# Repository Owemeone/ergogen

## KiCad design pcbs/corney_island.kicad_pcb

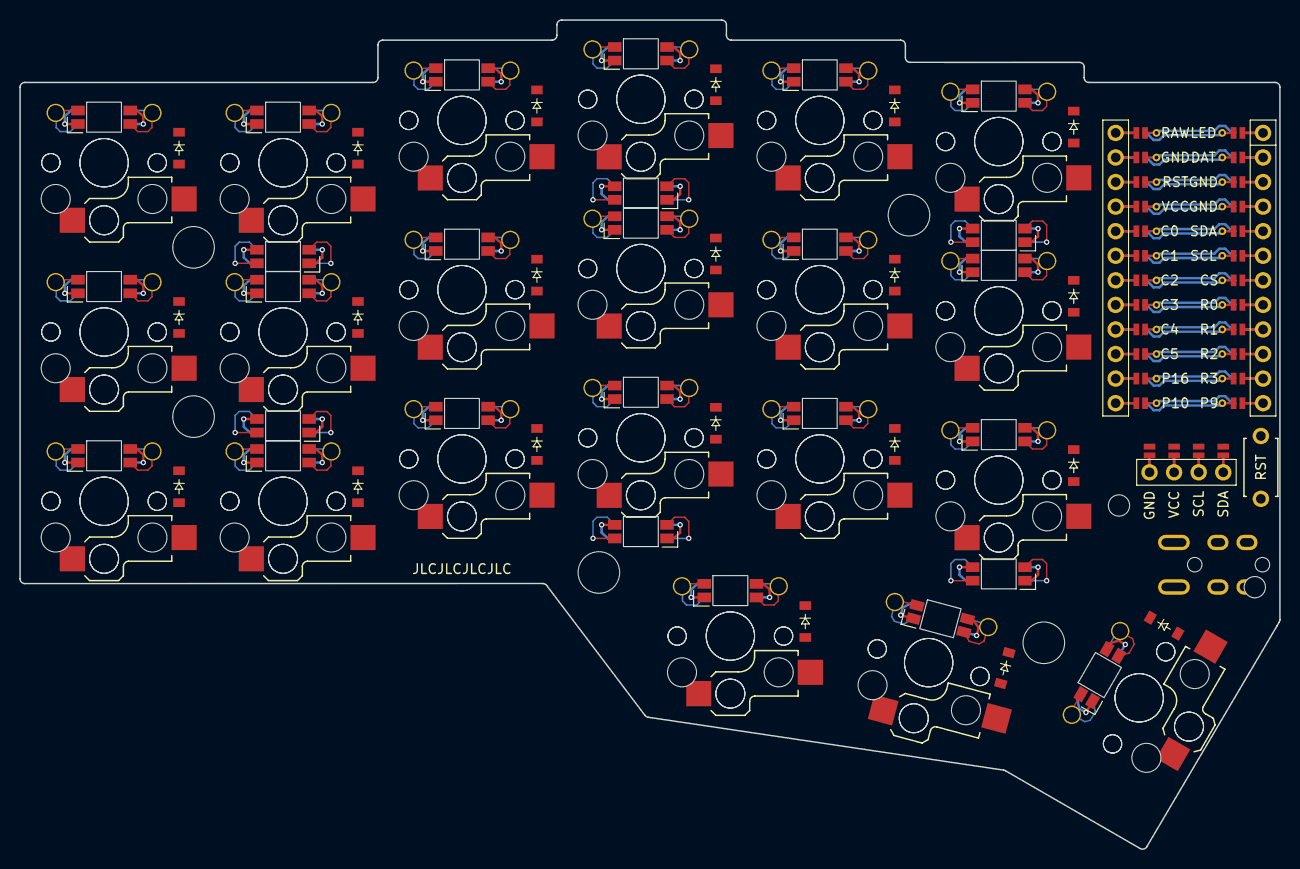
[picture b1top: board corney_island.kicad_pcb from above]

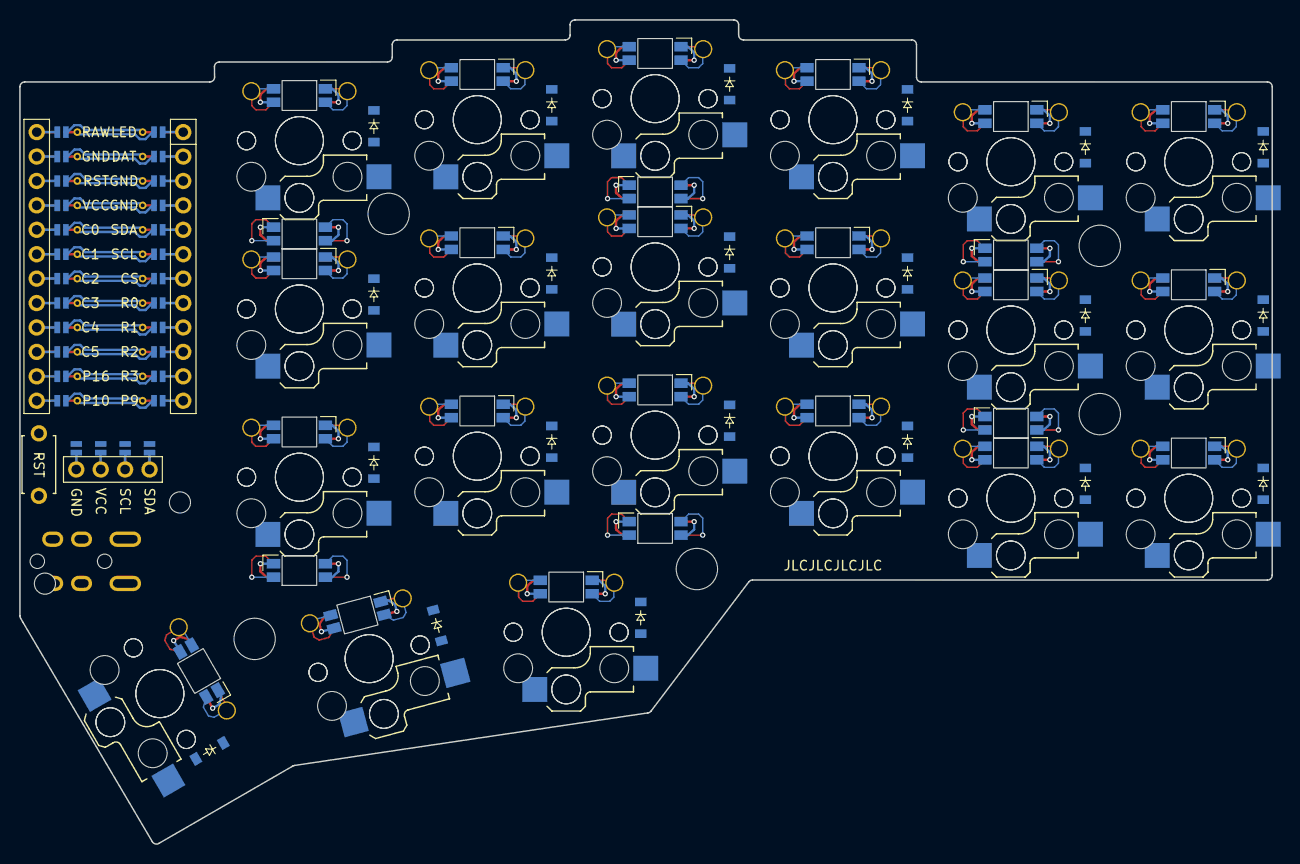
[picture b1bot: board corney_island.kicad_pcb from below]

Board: 2 copper layers, 130.3 x 85.7 mm, 122 parts (69 on the bottom side), 89 nets.

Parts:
D1, D2, D3, D4, D5, D6, D7, D8, D9, D10, D11, D12, D13, D14, D15, D16, D17, D18, D19, D20, D21, D22, D23, D24, D25, D26, D27, D28, D29, D30, D31, D32, D33, D34, D35, D36, D37, D38, D39, D40, D41, D42: diode_tht_sod123
DISP1: display_ssd1306
LED1, LED2, LED3, LED4, LED5, LED6, LED7, LED8, LED9, LED10, LED11, LED12, LED13, LED14, LED15, LED16, LED17, LED18, LED19, LED20, LED21: led_SK6812mini-e (per-key, reversible)
LED22, LED23, LED24, LED25, LED26, LED27: led_SK6812mini-e (underglow, reversible)
MCU1: mcu_nice_nano
MH1, MH2, MH3, MH4, MH5, MH6, MH7: mounting_hole_npth
RST1: reset_switch_tht_top
S1, S2, S3, S4, S5, S6, S7, S8, S9, S10, S11, S12, S13, S14, S15, S16, S17, S18, S19, S20, S21, S22, S23, S24, S25, S26, S27, S28, S29, S30, S31, S32, S33, S34, S35, S36, S37, S38, S39, S40, S41, S42: switch_choc_v1_v2
TRRS1: trrs_pj320a (reversible, symmetric)

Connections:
C0: MCU1.120, S1.1, S2.1, S3.1, S22.1, S23.1, S24.1
C1: MCU1.119, S4.1, S5.1, S6.1, S25.1, S26.1, S27.1
C2: MCU1.118, S7.1, S8.1, S9.1, S28.1, S29.1, S30.1
C3: MCU1.117, S10.1, S11.1, S12.1, S19.1, S31.1, S32.1, S33.1, S40.1
C4: MCU1.116, S13.1, S14.1, S15.1, S20.1, S34.1, S35.1, S36.1, S41.1
C5: MCU1.115, S16.1, S17.1, S18.1, S21.1, S37.1, S38.1, S39.1, S42.1
DAT: MCU1.102, TRRS1.3
DISP1_1: DISP1.1, DISP1.10, DISP1.23
DISP1_2: DISP1.2, DISP1.11, DISP1.22
DISP1_3: DISP1.3, DISP1.12, DISP1.21
DISP1_4: DISP1.4, DISP1.13, DISP1.20
GND: DISP1.14, DISP1.24, LED1.3, LED2.3, LED3.3, LED4.3, LED5.3, LED6.3, LED7.3, LED8.3, LED9.3, LED10.3, LED11.3, LED12.3, LED13.3, LED14.3, LED15.3, LED16.3, LED17.3, LED18.3, LED19.3, LED20.3, LED21.3, LED22.3, LED23.3, LED24.3, LED25.3, LED26.3, LED27.3, MCU1.103, MCU1.104, MCU1.123, RST1.2, TRRS1.2
LED: LED22.4, MCU1.101
LED_1: LED16.4, LED21.2
LED_2: LED16.2, LED17.4
LED_3: LED17.2, LED18.4
LED_4: LED15.4, LED18.2
LED_5: LED14.4, LED15.2
LED_6: LED13.4, LED14.2
LED_7: LED13.2, LED20.4
LED_8: LED19.4, LED20.2
LED_9: LED10.4, LED19.2
LED_10: LED10.2, LED11.4
LED_11: LED11.2, LED12.4
LED_12: LED9.4, LED12.2
LED_13: LED8.4, LED9.2
LED_14: LED7.4, LED8.2
LED_15: LED4.4, LED7.2
LED_16: LED4.2, LED5.4
LED_17: LED5.2, LED6.4
LED_18: LED3.4, LED6.2
LED_19: LED2.4, LED3.2
LED_20: LED1.4, LED2.2
R0: D3.1, D6.1, D9.1, D12.1, D15.1, D18.1, D24.1, D27.1, D30.1, D33.1, D36.1, D39.1, MCU1.108
R1: D2.1, D5.1, D8.1, D11.1, D14.1, D17.1, D23.1, D26.1, D29.1, D32.1, D35.1, D38.1, MCU1.109
R2: D1.1, D4.1, D7.1, D10.1, D13.1, D16.1, D22.1, D25.1, D28.1, D31.1, D34.1, D37.1, MCU1.110
R3: D19.1, D20.1, D21.1, D40.1, D41.1, D42.1, MCU1.111
RST: MCU1.122, RST1.1
SCL: DISP1.16, DISP1.26, MCU1.106
SDA: DISP1.17, DISP1.27, MCU1.105
ULED_1: LED22.2, LED23.4
ULED_2: LED23.2, LED24.4
ULED_3: LED24.2, LED25.4
ULED_4: LED25.2, LED26.4
ULED_5: LED26.2, LED27.4
ULED_6: LED21.4, LED27.2
VCC: DISP1.15, DISP1.25, LED1.1, LED2.1, LED3.1, LED4.1, LED5.1, LED6.1, LED7.1, LED8.1, LED9.1, LED10.1, LED11.1, LED12.1, LED13.1, LED14.1, LED15.1, LED16.1, LED17.1, LED18.1, LED19.1, LED20.1, LED21.1, LED22.1, LED23.1, LED24.1, LED25.1, LED26.1, LED27.1, MCU1.121, TRRS1.4
far_home_B: D21.2, S21.2
far_home_F: D42.2, S42.2
index_bottom_B: D13.2, S13.2
index_bottom_F: D34.2, S34.2
index_home_B: D14.2, S14.2
index_home_F: D35.2, S35.2
index_top_B: D15.2, S15.2
index_top_F: D36.2, S36.2
inner_bottom_B: D16.2, S16.2
inner_bottom_F: D37.2, S37.2
inner_home_B: D17.2, S17.2
inner_home_F: D38.2, S38.2
inner_top_B: D18.2, S18.2
inner_top_F: D39.2, S39.2
mid_home_B: D20.2, S20.2
mid_home_F: D41.2, S41.2
middle_bottom_B: D10.2, S10.2
middle_bottom_F: D31.2, S31.2
middle_home_B: D11.2, S11.2
middle_home_F: D32.2, S32.2
middle_top_B: D12.2, S12.2
middle_top_F: D33.2, S33.2
near_home_B: D19.2, S19.2
near_home_F: D40.2, S40.2
outer_bottom_B: D1.2, S1.2
outer_bottom_F: D22.2, S22.2
outer_home_B: D2.2, S2.2
outer_home_F: D23.2, S23.2
outer_top_B: D3.2, S3.2
outer_top_F: D24.2, S24.2
pinky_bottom_B: D4.2, S4.2
pinky_bottom_F: D25.2, S25.2
pinky_home_B: D5.2, S5.2
pinky_home_F: D26.2, S26.2
pinky_top_B: D6.2, S6.2
pinky_top_F: D27.2, S27.2
ring_bottom_B: D7.2, S7.2
ring_bottom_F: D28.2, S28.2
ring_home_B: D8.2, S8.2
ring_home_F: D29.2, S29.2
ring_top_B: D9.2, S9.2
ring_top_F: D30.2, S30.2

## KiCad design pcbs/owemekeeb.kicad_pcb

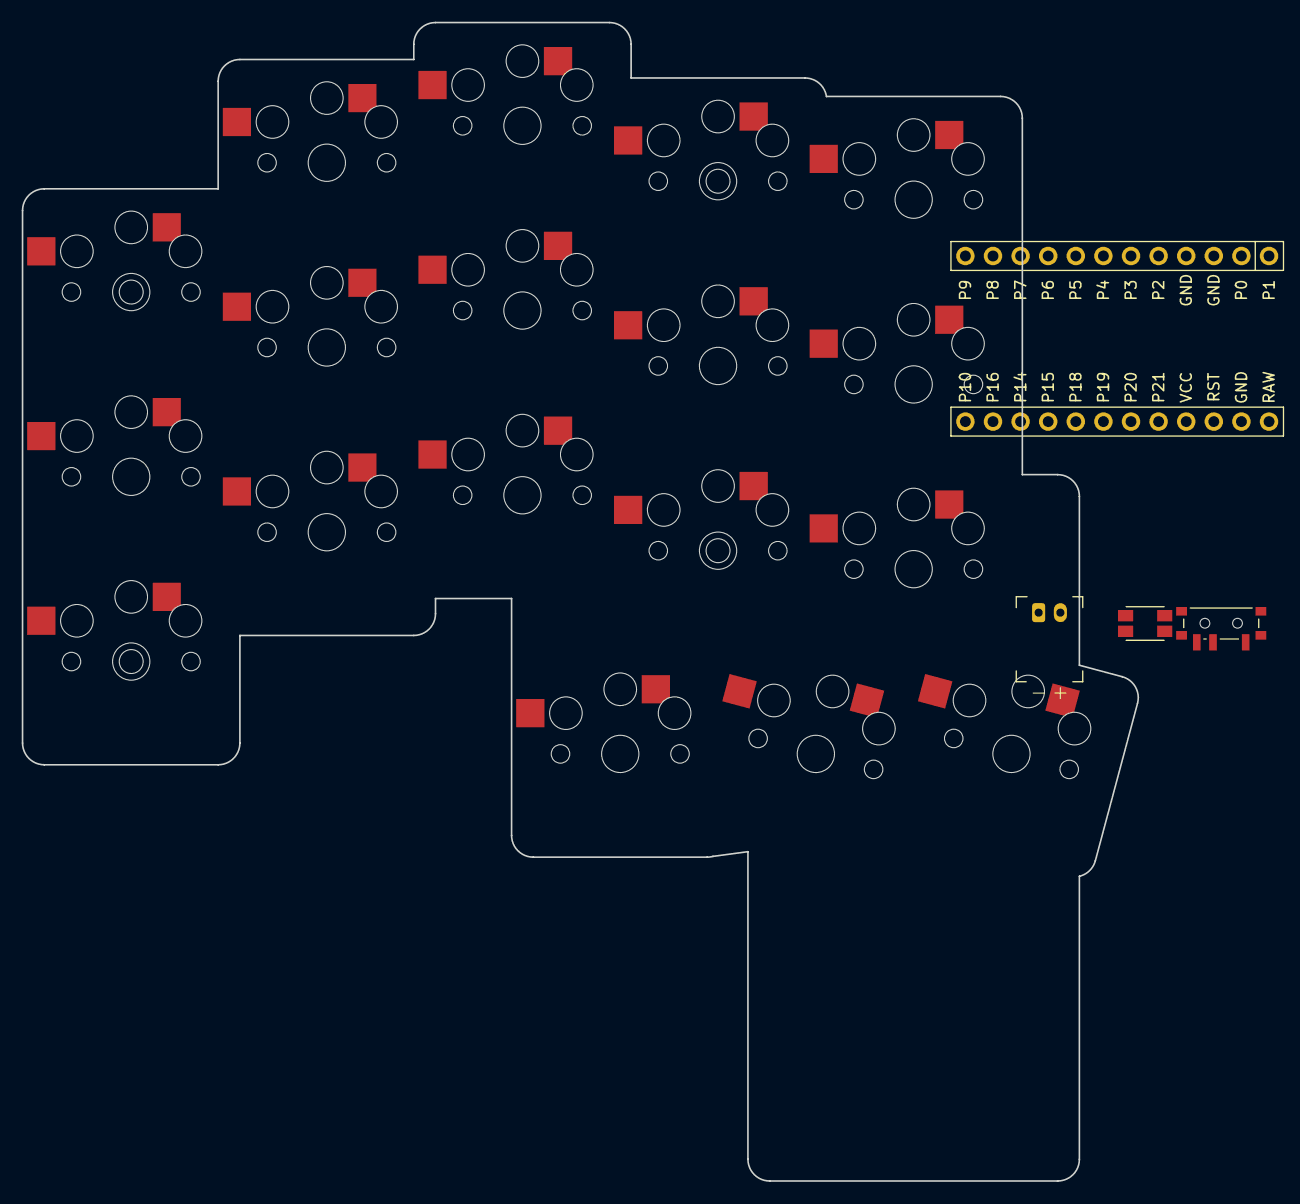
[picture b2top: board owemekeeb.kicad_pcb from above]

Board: 2 copper layers, 102.7 x 106.6 mm, 26 parts (0 on the bottom side), 22 nets, no tracks yet.

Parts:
JST1: battery_connector_jst_ph_2
MCU1: mcu_nice_nano
MH1, MH2, MH3, MH4: mounting_hole_npth
S1, S2, S3, S4, S5, S6, S7, S8, S9, S10, S11, S12, S13, S14, S15, S16, S17, S18: PG1350
SW1: power_switch
SW2: sw_reset_side

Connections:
GND: JST1.1, MCU1.2, MCU1.21, MCU1.22, S1.2, S2.2, S3.2, S4.2, S5.2, S6.2, S7.2, S8.2, S9.2, S10.2, S11.2, S12.2, S13.2, S14.2, S15.2, S16.2, S17.2, S18.2, SW2.1
P0: MCU1.23, S6.1
P1: MCU1.24, S9.1
P2: MCU1.20, S3.1
P3: MCU1.19, S8.1
P4: MCU1.18, S5.1
P5: MCU1.17, S2.1
P6: MCU1.16, S7.1
P7: MCU1.15, S4.1
P8: MCU1.14, S1.1
P9: MCU1.13, S16.1
P10: MCU1.12, S17.1
P14: MCU1.10, S13.1
P15: MCU1.9, S10.1
P16: MCU1.11, S18.1
P18: MCU1.8, S14.1
P19: MCU1.7, S11.1
P20: MCU1.6, S15.1
P21: MCU1.5, S12.1
RAW: MCU1.1, SW1.3, SW1.6
RST: MCU1.3, SW2.2
pos: SW1.2, SW1.5

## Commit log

2022-06-20 Add Owemekeeb
2022-06-20 Updated .gitignore
2022-06-20 package-lock changes
2022-06-21 Cleanup Use variables Better tracing of outline
2022-06-23 Add net class for power
2022-06-23 Update pin assignment
2022-06-24 Add build script based on Samoklava
2022-07-05 Update my keyboard
2022-07-05 Add reference values to vias Rotate PCM12
2022-07-05 Add Paintbrush config
2022-07-05 Add build script for Windows
2022-10-26 Added promicro_dave and workflows
2022-10-26 Minor fix
2022-10-26 Minor fixes again
2022-10-26 Case sensitive?
2022-10-26 temp output
2022-10-27 New steps in workflow - added DRC step - added image generation
2022-10-27 Continue on error for drc
2022-10-27 Upgrade deprecated actions
2022-10-27 Add name to gerber output
2022-10-27 Typo
2022-10-27 nametemplate isn't support in this version of kikit
2022-10-27 Add DRC to kikit fab
2022-10-27 Test DRC on samoklava
2022-10-27 update kikit
2022-10-28 Continue on error for export gerbers, because of drc
2022-10-28 Add workflows for all keyboards
2022-10-28 Error in build all yaml
2022-10-28 next attempt at matrix
2022-10-28 next attempt
2022-10-28 again
2022-10-28 more attempts
2022-10-28 and again
2022-10-28 typo again
2022-10-28 tryout
2022-10-28 keep trying
2022-10-28 How about this
2022-10-28 Wow that where a lot of omissions
2022-10-28 fail fast false
2022-10-28 Set maximum passes for autoroute
2022-10-28 disable drc on gerber export
2022-10-28 paintbrush didn't have a pcb
2022-10-28 Max passes routing
2022-10-28 Fix paintbrush
2022-10-28 Set max autoroute passes
2022-10-28 trying drc fix
2022-10-28 Reverted 0.01 attempt to fix DRC errors
2022-10-29 Attempt to fix drc error with choc footprint
2022-10-29 Fix owmekeeb workflow
2022-10-29 Type
2022-10-29 Add choc pretty
2022-10-29 Type again
2022-10-29 Newish choc pretty
2022-10-30 Fix keyboard array for all workflows
2022-10-30 Owemeone uses choc again
2022-10-30 Keyboard vs keyboards
2022-10-30 Ooops
2022-10-30 Rebuild on yaml change
2022-10-30 Repeat last
2022-10-30 Try to trigger build
2022-10-30 Guess what? Typo
2022-10-30 Trigger again
2023-08-08 Fix owmekeeb for v4
2023-08-08 Trying without a desktop.. That will work
2023-08-08 Skip old build
2023-08-08 Fix order
2023-08-08 Typo owemekeeb
2023-08-08 config import
2023-11-25 Fix update issues
2023-11-25 samples
2023-11-25 udpate promicro pretty
2023-11-25 fixes
2023-11-25 Add intersect aggregator (#102)
    * Added intersect aggregator
    * Addressed stylistic PR feedback
    * Set the rotation of the intersected point to the second point’s rotation
    * Revert "Set the rotation of the intersected point to the second point’s rotation"
    This reverts commit d210a98f79a8866519fc9695487a9ea235167b8b.
    * Adjusted aggregate function to not need axis1 and axis2 parameters
2023-11-25 Update running node version in build
2024-02-26 Update github workflow
2024-02-26 Shuffle footprints
2024-02-26 Move config to new 4.X folders
2024-02-26 More shuffling and make sure it sticks in gitignore
2024-02-26 Path issue
2024-02-26 Renames
2024-02-26 Update actions versions
2024-02-26 Fix cases outline name
2024-02-26 Sure this will blow up
2024-02-26 Fix docker version
2024-02-26 update makerjs
2025-07-08 configs
2025-07-08 better dear?
2025-07-08 template?
2025-07-08 woops
2025-07-09 Is github faster?
2025-07-09 Change
2025-07-09 Blablabla
2025-07-09 Test
2025-07-09 Woop
2025-07-09 Tralalala
2025-07-09 passes
